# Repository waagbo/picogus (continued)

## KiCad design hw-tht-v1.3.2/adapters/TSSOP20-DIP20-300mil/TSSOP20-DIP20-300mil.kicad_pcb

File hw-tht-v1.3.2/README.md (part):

# PicoGUS THT (through-hole) v1.3.2 – based on PicoGUS v1.2

Board revision **v1.3.2**: the [v1.3.1 (rev B) THT board](../hw-tht-v1.3.1/README.md) on a 102 mm outline, with
the fine-pitch chips soldered straight to the card and a test pad on every one of their pins.

* **U3/U4** (SN74CB3T3257, TSSOP-16) and **U9** (PCM5100A, TSSOP-20) only exist as TSSOPs. They are soldered to
  the card on hand-solder footprints, and **every pin has its own 0.7 mm round test pad** in line with it, for a
  probe, a meter or a scope (see [U3/U4 and U9 with a test pad per pin](#u3u4-and-u9-with-a-test-pad-per-pin)).
  The TSSOP-to-DIP adapter boards of the earlier v1.3.2 layout are gone, and so are their sockets.
* **The GY-PCM5102 module option (J10) is gone.** The on-board DAC is always fitted.
* **New placement** of the DAC block, the mixer and the jacks (2026-10-31 / 2026-11-01): the DAC sits above U3/U4
  with its analog side facing east toward the output filter and the mixer above it, MIDI OUT at the top of the
  bracket end and LINE OUT below WT VOL (see [Placement](#placement)).
* **C36** (U9 charge-pump decoupling) is a through-hole 0.1 µF disc, and all eight DAC decoupling discs sit on the
  side of U9 where their pins are (see [DAC decoupling](#dac-decoupling)).
* **C8/C10** (U8 PSRAM decoupling) are the v1.3.1 through-hole discs, next to U8.
* **1.84 mm shorter**: 102.0 mm long over the outline (v1.3.1: 103.8 mm), trimmed at the bracket end. The bracket tab
  holes H1/H2 are 1.70 mm further from the bracket plate, so the card needs a bracket with longer tabs (see
  [Bracket](#bracket)).
* **No artwork on the back silkscreen**: the princess artwork is to be UV printed instead. The back texts stay.

The main board is through-hole apart from **U3, U4, U9** (TSSOP, 0.65 mm pitch), **U8** (APS6404L PSRAM, SOIC-8,
1.27 mm pitch) and the optional **U12** (USBLC6-2SC6, SOT-23-6), all on the front. The rest of the circuit is
v1.3.1's: USB-A host port, Waveblaster header, op-amp mixer.

> **Status: v1.3.2, ready to order (tag `hw-tht-v1.3.2`); not built or tested yet.** The placement of 2026-11-01 is
> routed on two layers (2026-11-01).
> The schematic's ERC is the same as v1.3.1's (280 warnings, 0 errors). DRC with schematic parity finds 0
> unconnected items and, as errors, only the 12 accepted courtyard overlaps in the logic column, so
> `hw-common/tools/jlcpcb.sh` exports with `FORCE=1`; `build/jlcpcb/` holds that export (not in git: the repository
> ignores `build/`). The first routed TSSOP layout (commit 298e993) was reviewed independently; this placement
> shortens the DAC outputs and the mixer's summing nodes that review pointed at, and its route applies the review's
> rules from the start. Compared with the routed DIP-adapter layout (commit d5c4a85) it is better on I2S, the
> DAC-to-mixer path and the vias at silkscreen text, and worse on the ISA data-bus length, which the test pads set:
> see [Layout status](#layout-status).

Files:

| File | What |
|---|---|
| `PicoGUS-THT.kicad_pro/.kicad_sch/.kicad_pcb` | KiCad **10** project (the root sheet is the v1.2 logic). The board is routed |
| `audio.kicad_sch` | PCM510x DAC sheet: U9 a TSSOP-20 with test pads, C36 a THT disc, no J10 |
| `wavetable.kicad_sch` | Waveblaster header, WT volume, op-amp mixer, line-out jack (as v1.3.1) |
| `usb.kicad_sch` | USB host port (J11 USB-A, F1, C34/C35, U12) (as v1.3.1) |
| `PicoGUS-THT-schematic.pdf` | Schematic PDF |
| `BOM-THT.csv` | BOM with DigiKey **and** LCSC part numbers and a digikey.no link per line (v1.3.0 lines checked 2026-09-28, rev B lines 2026-10-18, v1.3.2 lines 2026-10-23) |
| `BOM-THT-digikey-upload.csv` (+ `-optional`, `-10x`) | DigiKey cart/BOM upload with the reference designators as Customer Reference; optional: sockets, U12 |
| `BOM-THT-sockets.csv` (+ `-digikey-upload`, `-10x`) | Socket build: every DIP IC and the Pico socketed, with heights (see [Socket build](#socket-build)) |
| `docs/renders/` | 3D renders of the routed card from the front and the back, in red, purple, black and blue solder mask (ENIG, white silkscreen) |
| `docs/figures/` | Figures for the README's exceptions and design choices (e.g. the test pads, the placement options, the accepted courtyard overlaps), with the scripts that make them in `docs/figures/src/` |

The shared `PiGUS library` symbols and footprints are linked from `hw-common/`, like the other boards. **New in the
shared library for v1.3.2:** `TSSOP-16_4.4x5mm_P0.65mm_HandSolder_TestPads` (U3, U4),
`TSSOP-20_4.4x6.5mm_P0.65mm_HandSolder_TestPads` (U9) and `RPi_Pico_SMD_TH_USB_NoSWD` (U1, see
[102 mm board](#102-mm-board)), in `hw-common/PiGUS library.pretty`; DRC's library check finds the board's U1, U3,
U4 and U9 identical to them. The adapter footprints and adapter 3D models of the earlier v1.3.2 layout are removed;
the older `DIP-16_W7.62mm_TSSOP-16_Nested` stays unused.

Every part has a 3D model. The ones KiCad 10's library does not have are in `hw-common/parts`, reached through the
project folder's `parts` link: the CUI SJ1-3535NG jacks (J8 green; J5 a black copy of the same CUI model), the Alps
RK09712 pot (RV1) and a simple generated Bourns MF-R050 (F1). U3/U4/U9 use KiCad's TSSOP models, U1 KiCad's own
`RaspberryPi_Pico.step`, and J9's header model path is fixed. The library footprints carry the same models as the
board.

## What changed compared to v1.3.1

### U3/U4 and U9 with a test pad per pin

| | U3, U4 (SN74CB3T3257, TSSOP-16) | U9 (PCM5100A, TSSOP-20) |
|---|---|---|
| Footprint | `PiGUS library:TSSOP-16_4.4x5mm_P0.65mm_HandSolder_TestPads` | `PiGUS library:TSSOP-20_4.4x6.5mm_P0.65mm_HandSolder_TestPads` |
| Courtyard | 11.4 × 5.75 mm | 11.4 × 7.05 mm |
| Position (centre) | U3 (150.22, 110.10), U4 (161.44, 110.12), both 90° (pin 1 at the bottom left) | (156.10, 84.53), 180° (pin 1 at the bottom right) |

* **Land pattern**: the TSSOP hand-solder pads (1.775 × 0.40 mm at ±3.01 mm from the centre, toes out to ±3.9 mm),
  long enough to put an iron on each pin.
* **One test pad per pin**: a 0.7 mm round pad (bare copper, `testpoint` property) straight out from each pin,
  joined to it by a 0.2 mm track. The pads alternate between two columns, 4.45 and 5.10 mm from the centre, so each
  sits on its own pin's line and 1.3 mm from the next pad in its column; the track to an outer pad passes between two
  inner pads with 0.2 mm on each side, the board's normal clearance. The footprint has the pin numbers at the column
  ends in 0.8 mm silk. The pads make every pin reachable for a probe, a meter or a scope clip, and a solder bridge
  between two pins shows up as a short between their pads.
* **Routing**: an outer-column pin is routed from its test pad. An inner-column pin that is used gets a 0.2 mm
  escape stub straight on from its test pad, centred between the two outer pads, to 5.80 mm from the centre, and is
  routed from the stub end (26 stubs; the two left unused are removed after routing, see
  [Layout status](#layout-status)). The router cannot squeeze a track between two outer pads (0.6 mm
  gap) any other way, and the stubs keep the 0.2 mm clearance exactly as the pin-to-pad tracks do.
* **Pin numbers stay the schematic's**: U9 is 1 CPVDD, 2 CAPP, 3 CPGND, 4 CAPM, 5 VNEG, 6 OUTL, 7 OUTR, 8 AVDD,
  9 AGND, 10 DEMP, 11 FLT, 12 SCK, 13 BCK, 14 DIN, 15 LRCK, 16 FMT, 17 XSMT, 18 LDOO, 19 DGND, 20 DVDD.
* The symbols' `Adapter` fields and the adapter wording in the descriptions and sheet notes are gone; the root sheet
  says "SMD: U3/U4 TSSOP-16, U9 TSSOP-20 (with test pads), U8 SOIC-8, U12 opt.".

![Test pads on U9 (and U3/U4): the TSSOP-20 land pattern to scale with its 20 test pads in two staggered columns
(inner 4.45 mm, outer 5.10 mm from the centre, 1.3 mm between two pads of a column), the 0.2 mm track from each pin
to its pad passing between two pads with 0.2 mm clearance on each side, and the escape stubs that carry an
inner-column pin out between two outer pads to the routing](docs/figures/test-pads.png)

### No GY-PCM5102 module option

J10 (the GY-PCM5102 module, soldered on male pins over the DAC area as the alternative to the on-board DAC since
v1.3.0) is gone from the schematic and the board. Its dashed silkscreen outline and the "DAC -OR- GY-PCM5102"
heading went with it; the heading now just says "DAC". Its nets (BCK, DIN, LRCK, +5V, GND, AUDIO_L/R) stay,
because U9's circuit uses them. U9, C12–C20, C36, FB3, R7 and R8 are always fitted. The BOM's J10 line and its
"DAC AREA: leave out ..." notes are gone.

### DAC decoupling

C36 (U9 CPVDD decoupling) is the board's standard 0.1 µF 50 V X7R radial disc (Murata RDER71H104K0M1H03A, the 0.1 µF
line of the BOM) instead of v1.3.1's 0603. U9 stands at 180° with its analog pins 1–10 facing east, toward the output
filter and the mixer, and its digital pins 11–20 facing west. Each disc sits on the side of the pins it serves:

* **East, beside pins 1–10**, in rows 3.0 mm apart: C15 (AVDD, 10 µF) and C13 (AVDD) at the top, the output
  resistors R8/R7 level with pins 7/6, then C16 (CAPP/CAPM) and C17 (VNEG); the filter discs C20/C19 end the C13 and
  C16 rows on the east.
* **South, under pins 1–3**: C36 (CPVDD/CPGND), with C14 (+3V3) below it.
* **West, beside pins 11–20**: C18 (LDOO) level with pins 17–19 and C12 (DVDD) below pin 20. FB3 (the AVDD bead)
  runs along the top of the block from the +3V3 side in the west to its AVDD pad above C15.

Distances from the chip pin to the nearest pad of the part, straight line:

| Part | Pins | DIP-adapter layout (d5c4a85) | First routed TSSOP layout (298e993) | Now |
|---|---|---|---|---|
| C36 | CPVDD (1) / CPGND (3) | 2.7 / 9.2 mm | 9.7 / 5.6 mm | 3.6 / 5.4 mm |
| C16 | CAPP (2) / CAPM (4) | 3.2 / 3.2 mm | 9.5 / 4.6 mm | 9.7 / 5.5 mm |
| C17 | VNEG (5) | 6.6 mm | 9.6 mm | 8.1 mm |
| C13 | AVDD (8) / AGND (9) | 4.7 / 6.7 mm | 5.1 / 9.6 mm | 5.6 / 9.9 mm |
| C15 | AVDD (8) | 7.3 mm | 12.4 mm | 7.8 mm |
| C18 | LDOO (18) / DGND (19) | 3.5 / 9.1 mm | 4.5 / 9.5 mm | 4.0 / 9.0 mm |
| C12 | DVDD (20) / DGND (19) | 4.5 / 8.4 mm | 2.6 / 6.4 mm | 5.4 / 3.8 mm |
| R7 / R8 | OUTL (6) / OUTR (7) | 3.0 / 2.8 mm | 6.8 / 8.2 mm | 4.7 / 4.6 mm |
| FB3 | AVDD (8) | 2.8 mm | 14.1 mm | 6.3 mm |

* **C36 is the nearest disc to its pin** (3.6 mm from CPVDD), as the PCM510x datasheet asks for the charge-pump
  supply. C16 (the flying capacitor between CAPP and CAPM) stays 9.7 mm from CAPP: it shares the east column with
  the output resistors, which sit level with their pins.
* C16 and C17 were 0.02 mm off the 3.0 mm row grid in the uploaded placement (y 88.60 / 91.60), so C16's courtyard
  touched R7's by 0.015 mm; they are now at y 88.62 / 91.62, in line with C19.
### C8/C10: through-hole discs next to U8

| Ref | Part | DigiKey | LCSC |
|---|---|---|---|
| C8 | 0.1 µF 50 V X7R radial disc, 5.0 mm pitch, Murata RDER71H104K0M1H03A (the BOM's 0.1 µF line) | 490-9144-1-ND | C527620 |
| C10 | 1 µF 50 V X7R radial disc, 5.0 mm pitch, Murata RDER71H105K2M1H03A | 490-9146-1-ND | C1620132 |

These are the v1.3.1 parts again (the routed layout of commit 8dbb6c6 had 0805s on the back under U8). U8 (SOIC-8,
front) stands at 90° at (190.00, 92.47): pins 1–4 along the bottom (y 94.95, pin 1 at the left), pins 5–8 along the
top (y 90.00), pin 8 (+3V3) at (188.09, 90.00), pins 3/4/7 GND. C8 (0.1 µF) stands vertically left of U8, its +3V3
pad 2.50 mm straight left of pin 8 at (185.59, 90.00) and its GND pad at (185.59, 95.00); C10 (1 µF) lies above U8,
+3V3 pad at (187.09, 87.00), GND pad at (192.09, 87.00). With them, every SMD part (U3, U4, U8, U9, U12) is on the
front.

### 102 mm board

The bracket end of the outline is trimmed 1.84 mm (x 220.13 → 218.29). The board is 101.90 × 99.85 mm at the
outline's line centres, 102.00 × 99.95 mm over its 0.1 mm lines (v1.3.1 and the routed v1.3.2 layout: 103.74 ×
99.85 / 103.84 × 99.95 mm). JLCPCB quoted USD 24.50 for 10 black ENIG 2-layer boards at 102.0 mm (and 101.9 mm), USD 33 at
102.7 mm and 33.53 at 103.74 mm (2026-10-28). The ISA fingers, the other three edges and the bracket plate's place in the case do not change.
To keep copper at least 0.35 mm from the new edge, these parts moved left, away from the bracket:

| Part | Moved | Now | Nearest copper to the new edge |
|---|---|---|---|
| H1 / H2 (bracket tab holes) | 1.70 mm | x 214.70 | 0.39 mm (their 6.4 mm pads) |
| J5 (MIDI out) | 1.10 mm | x 217.00 | 0.39 mm (sleeve pad) |
| J8 (line out) | 0.90 mm | x 217.00 | 0.39 mm (sleeve pad) |
| U1 (Pico), with its five test-pad rule areas and its two micro-USB relief slots | 1.35 mm | centre x 192.88, pin 1 (217.01, 100.00) | 0.36 mm (TP2/TP3); the slots (centre x 216.88) end 0.41 mm from the edge |
| U4 / U3 | – | TSSOP centres x 161.44 / 150.22 (re-placed for the soldered TSSOPs, see [Placement](#placement)) | – |

J11 and RV1 stay where they were. The distances are to the outline's line centre. Between these parts and the edge
there is no room for a track or a via: 0.3 mm copper-to-edge, a 0.2 mm track and 0.2 mm clearance need 0.7 mm. What
the trim means for the bracket is under [Bracket](#bracket): the tab holes need a bracket with 1.70 mm longer tabs.

![The bracket end trimmed from 103.74 to 101.90 mm: old (dashed) and new outline with the trimmed 1.84 mm strip, the
bracket plate and tabs from User.Drawings, the tab holes H1/H2 1.70 mm further in (7.03 mm from the plate instead of
5.33), J5, RV1, J8, J11 and the Pico's USB end with their moves and nearest copper to the new edge, and a table of the
x positions](docs/figures/bracket-trim.png)

* **U1 uses the new footprint `PiGUS library:RPi_Pico_SMD_TH_USB_NoSWD`**: `RPi_Pico_SMD_TH_USB` without the
  three SMD castellation pads at the SWD end (pads 41–43: SWCLK and SWDIO, both not connected, and GND; their
  through-holes stay) and with the courtyard 0.2 mm past the module there instead of 0.5 mm. With the old
  courtyard, U4's would overlap the Pico's by 0.25 mm.
* The Pico's USB end (x 218.38) is now flush with the edge: 0.09 mm past the outline's line centre (0.40 mm inside
  it before).
* The Pico's far end is at x 167.38, 2.9 mm under a full-size Waveblaster daughterboard's outline (x 170.32; routed
  v1.3.2 layout 1.6 mm, v1.3.1 1.3 mm). That matters for a socketed Pico (see [Socket build](#socket-build)).

### Placement

The board holds a hand arrangement on the 102 mm outline: the logic column and the Pico from 2026-10-28, the jack
arrangement for the soldered TSSOPs from 2026-10-31, and the DAC block and mixer as rearranged on 2026-11-01 after a
first route, routed afterwards (see [Layout status](#layout-status)).

* **Logic column at the left edge** (as on the earlier v1.3.2 layout). U10, U7, U6 and U5 (DIP-14, 90°, pin 1 at the
  left as on v1.3.1) are stacked in line with U2 at x 120.07, 12.05 mm apart (pin 1 at y 65.62 / 77.67 / 89.71 /
  101.76; U2: 113.81). Each chip's decoupling cap lies horizontally (0°) in the gap above it, pad 1 2.21 mm straight
  above the supply pin (pin 14; U2: pin 20): C21 (U10, +5V), C6 (U7), C9 (U6), C7 (U5) and C4 (U2), pads at x
  120.07 / 125.07, y 55.79 / 67.83 / 79.88 / 91.93 / 103.97. R18, R5, R6 and R17 stand vertically (−90°) in one
  column at x 138.60, at the chips' right-hand ends (pad 1 at y 56.73 / 68.78 / 80.82 / 92.87). The column is
  packed tighter than the courtyards allow: 12 overlaps, accepted (see [Layout status](#layout-status)). The five
  references stand vertically at the board edge (x 117.50), centred on each chip.
* **U2** (DIP-20, 90°) at the lower left, pin 1 (120.07, 113.81). **J1** (the IRQ/DMA jumper block) at pin 1
  (136.03, 124.91), 90°, with its `IRQ`/`DMA` labels and numbers above it.
* **U3/U4** (TSSOP-16 with test pads, 90°): U3 (D0–D3, A0–A3) at (150.22, 110.10) and U4 (D4–D7, A4–A7) at
  (161.44, 110.12), pin 1 at the bottom left. Their decoupling discs C3/C5 lie above them at y 102.29 (C3's +3V3 pad
  at x 147.88, 4.8 mm from U3's pin 16), R2 at (160.97, 99.01).
* **DAC block, above U3/U4 and the Pico's far end**: U9 (TSSOP-20 with test pads) at (156.10, 84.53), 180°: pins
  11–20 (I2S, LDOO, DGND, DVDD) on its west side, pins 1–10 (charge pump, VNEG, outputs, AVDD, AGND) on its east side,
  facing the output filter and the mixer. East of it, in rows 3.0 mm apart (see [DAC decoupling](#dac-decoupling)):
  C15 (163.60, 76.53), C13 (168.60, 79.53), R8 (163.60, 82.60), R7 (163.62, 85.62), C16 (168.60, 88.62) and C17
  (163.60, 91.62), with the filter discs C20 (170.70, 79.53) and C19 (170.70, 88.62) at the east end. C36 (161.00,
  90.50) and C14 (156.00, 93.50) lie under U9's pins 1–3, C18 (149.10, 86.03) and C12 (153.60, 90.53) on its west
  side, and FB3 (the AVDD bead) along the top at (148.60, 77.03). `DAC` stands at (146.11, 92.10).
* **Mixer, above the DAC block**: U11 (DIP-8, 0°) at (173.00, 61.00), its feedback discs C30/C31 standing (90°) at
  its two ends, (170.12, 65.08) and (183.50, 67.00); C28 (+12VA) above it at (180.62, 54.08) and C29 (−12VA) below at
  (175.62, 75.08); R23/R24 (±12V 10 Ω) at (170.42, 57.50) / (170.42, 72.00); C32/C33 (47 µF) standing at x 184.62
  (y 57.12 / 70.08). The mixer resistors stay in two columns: R13, R11, R22, R10, R21 at x 189.43 (y 54.50 / 58.00 /
  65.00 / 72.50 / 79.50) and R20, R12, R19 at x 199.58 (y 61.50 / 69.00 / 76.00). `MIXER` at (171.12, 55.04).
* **C22/C23** (the 10 µF bipolar Waveblaster coupling caps) stand at the top next to J9, (174.00, 40.00) and
  (181.50, 40.00), −90°, with their references above them at y 38.00. C22's can is 0.48 mm outside a full-size
  daughterboard's outline (x 170.32) at nominal size.
* **Bracket end, top to bottom: MIDI OUT, WT VOL, LINE OUT.** J5 (MIDI out) at (217.00, 49.00) with its parts
  R3 (176.64, 46.50), R4 (186.80, 50.50), FB1 (189.50, 46.50) and FB2 (189.50, 50.50) along the top; RV1 (WT VOL)
  at (214.00, 61.40); J8 (line out) at (217.00, 75.50). The labels
  `MIDI OUT`, `WT VOL` and `LINE OUT` are left-aligned at x 204.0 (y 43.5 / 65.0 / 70.0).
* **USB host corner**: U8 (SOIC-8) at (190.00, 92.47), 90°, with C8/C10 next to it (see
  [C8/C10](#c8c10-through-hole-discs-next-to-u8)); U12 at (197.14, 91.45), F1 vertical at (204.00, 90.00), C35 at
  (200.00, 95.00), C34 at (202.30, 83.50).
* **Waveblaster side**: R16 at (150.00, 46.00), 0°; C24, C25 and C26 in a row at y 45.50 (x 146.90 / 143.00 /
  139.00).
* **Pico (U1)** at (192.88, 108.89), pin 1 (217.01, 100.00), and the bracket end (H1/H2, J11) as on the earlier
  v1.3.2 layout (see [102 mm board](#102-mm-board)).

**Why this arrangement.** Four placements of the DAC, mixer and jacks were compared before the first route, each
with the DAC discs on their pins and the logic-column labels as above: A (the first hand placement, DAC block high in
the middle), A2 (A with a DAC block turned 90°), C (that block in the middle with the mixer beside it) and D. In A2
and C, U9's I2S pins face away from the Pico, and a trial route of the three I2S nets alone (with the DAC outputs kept
clear) needed 232 and 238 mm; in A 171 mm; in D 122 mm. D had the shortest DAC-to-mixer path and the shortest
ratsnest overall and was routed first (commit 298e993). That route left the mixer's summing nodes 51 / 53 mm long
and the DAC outputs 19 / 20 mm, because the output filter sat above U9 and the mixer inputs far from U11. The
present arrangement keeps D's jacks and moves the DAC block 12.9 mm west with the output filter east of U9, between
it and the mixer, and turns U11 so that its feedback discs sit on its pins. Against D, in ratsnest length: summing
nodes 95.7 → 61.9 mm, DAC outputs 18.5 → 9.5 mm, mixer outputs 64.3 → 41.5 mm, AVDD and LDOO 26.5 → 15.6 mm; I2S
113.6 → 123.5 mm and the Waveblaster path behind C22/C23 56.0 → 75.4 mm are longer; all nets but GND 4229 → 4169 mm.

![The comparison before the first route (D became commit 298e993; the present arrangement grew out of it). Placements A, A2, C and D side by side: board outlines with the DAC area and the mixer area shaded, the I2S
ratsnest, the audio-path ratsnest and the digital ratsnest that crosses the DAC area, and a table of the trial I2S
route, I2S ratsnest, distances from the DAC area to the Pico and U8, digital ratsnest through the DAC and mixer areas,
DAC-to-mixer and Waveblaster paths, mixer summing nodes, line out, ±12V, SPI and total ratsnest](docs/figures/placement-options.png)

| Part | Routed DIP-adapter layout (d5c4a85) | Now |
|---|---|---|
| U3 / U4 | DIP-16 adapter pin 1 (146.53, 106.42) / (157.74, 106.44), 0° | TSSOP-16 centre (150.22, 110.10) / (161.44, 110.12), 90° |
| U9 | DIP-20 adapter pin 1 (146.00, 78.30), 90° | TSSOP-20 centre (156.10, 84.53), 180° |
| U11 | (173.02, 51.10), 90° | (173.00, 61.00), 0° |
| J5 (MIDI) / J8 (line out) | (217.00, 75.50) / (217.00, 49.10) | (217.00, 49.00) / (217.00, 75.50) |
| U8 | (189.00, 93.90), 0° | (190.00, 92.47), 90° |
| C8 / C10 | (191.50, 88.40) / (184.00, 88.40), 180° | (185.59, 90.00), −90° / (187.09, 87.00), 0° |
| J1 | (120.00, 123.70) | (136.03, 124.91) |
| FB3 | (164.10, 93.73), 90° | (148.60, 77.03), 0° |
| C3 / C5 | (153.50, 103.28) / (164.69, 103.34), 180° | (147.88, 102.29) / (158.88, 102.29), 0° |

Positions are footprint origins (pin 1 for the DIPs, the centre for the TSSOPs), in mm. 51 of the 88 footprints moved
against the DIP-adapter layout (29 against the first routed TSSOP layout, 298e993); the logic column, U1, U2, the Waveblaster header and the bracket-end parts other
than J5/J8 did not.

### Silkscreen and back artwork

* Front `v1.3.2`, back `PicoGUS v1.3.2`.
* **Label font: Jost, embedded in the board file.** The 21 board labels (`WAVEBLASTER`, `MIXER`, `DAC`, `v1.3.2`,
  `LINE OUT`, `WT VOL`, `MIDI OUT`, `UART`, `USB PWR`, `IRQ`/`DMA` and their numbers, `< REAR`) use Jost Medium and
  Bold ([indestructible-type/Jost](https://github.com/indestructible-type/Jost), SIL Open Font License 1.1; the
  copyright and licence are in the font files' metadata), embedded with the board's embedded-fonts option. KiCad
  therefore shows and plots them the same on every machine, with or without the font installed. They were in
  Futura, inherited from v1.2, which was not embedded: each machine plotted its own substitute (DejaVu Sans or Inter
  in the cloud sessions that made the earlier gerbers). Futura cannot be embedded: Futura PT is marked
  "Preview & Print" only, so KiCad refuses it, and its licence forbids sharing the files. Jost is a free
  Futura-style face and looks almost the same at this size. Embedding adds about 120 KB to the board file. The
  v1.3.1 and v1.3.0 boards still use un-embedded Futura.
* **No princess artwork on the board.** It is removed from the back silkscreen and is to be UV printed on the back
  instead (source: `hw-common/art/princess.svg`; the routed v1.3.2 layout had it at 52.8 × 27.0 mm, v1.3.1 at
  71.6 × 37.0 mm). The back text block (version, copyright, licence, URL, thanks, dedication) and `< REAR` stay.
* **Front copper logo moved.** The exposed-copper PicoGUS logo (F.Mask openings over the front GND pour, with a rule
  area that keeps tracks and vias out) is turned horizontal and sits along the top edge above `LINE OUT`, x
  185.9–211.6, y 37.8–40.6, with `v1.3.2` right of it at (214.1, 40.0). Before, the logo stood vertically at the left
  edge (x 118.3–121.1, y 43.5–69.3) and `v1.3.2` at (120.5, 40.5). The pour under it is filled, so the logo shows
  copper.
* Labels placed by hand (2026-10-31; `MIXER`, `DAC` and C22/C23 on 2026-11-01). `MIXER` (171.12, 55.04) and `DAC`
  (146.11, 92.10) are centred, 1.2 mm high
  like the bracket-side labels (`DAC` was vertical at (186.3, 74.5) on v1.3.1). `WAVEBLASTER` is 1.2 mm (was 0.8),
  centred at (143.65, 37.5). `MIDI OUT`, `WT VOL` and `LINE OUT` are left-aligned at x 204.0 (y 43.5 / 65.0 / 70.0),
  `UART` and `USB PWR` at x 208.2 (y 121.5 / 126.0), so `UART` no longer touches J6's outline. The references of the
  logic column (U10, U7, U6, U5, U2) stand vertically at the board edge (x 117.50), centred on each chip; the
  references of the discs sit in the middle of each disc. The references of C22, C23, C32, C33, C34, U8, U12 and J11
  were placed by hand (C22's and C23's above their cans at y 38.00); U8's stands at (185.00, 88.00), nearer C10 than U8, and U12's is 0.08 mm from neighbouring silk.
  `< REAR` moved 1.70 mm left with H1/H2, its arrow tip still in line with them.
* **No via hole in any label**: the router counted every front and back silk text as a no-via area, so no via hole
  is within 0.10 mm of any text (the earlier routed layout had 13).
* v1.3.1's U12 pin-1 dot, left behind at (201.5, 89.7) next to F1 when U12 moved, is removed.
* Silkscreen DRC (with silk_over_copper/silk_overlap enabled): 45 silk_over_copper, all from the outlines of the
  decoupling discs in the logic column crossing the neighbouring DIP pads (`jlcpcb.sh` plots the silkscreen with the
  mask openings subtracted, so none of it prints on a pad); 2 silk_overlap (the IRQ/DMA divider line over J1 twice,
  as on v1.3.1); 19 silk_edge_clearance (J8, J5, RV1, J11 and the Pico's outline at
  the bracket end).

### Other

* Title blocks say v1.3.2 (root sheet and board 2026-10-28, the other sheets 2026-10-23). The schematic notes about
  the GY module and the SMD parts are updated, and `PicoGUS-THT-schematic.pdf` is plotted from the current schematic.
* No reference designator changed and none is new; J10 is the only one removed. The design rules and net classes
  are v1.3.1's (the `.kicad_pro` is unchanged).
* The schematic fields of C8/C10 name the Murata discs again (as on v1.3.1), and U1's footprint field is
  `PiGUS library:RPi_Pico_SMD_TH_USB_NoSWD`.
* 32 footprints (the wavetable sheet set, FB3, RV1, U11) still carried symbol links (KIID paths) from before the
  v1.3.0 schematic rebuild; DRC parity had only matched them by reference. They are re-linked to their symbols, so
  "Update PCB from schematic" keeps them.
* The U3/U4/U9 symbols point at the new TSSOP footprints with test pads; their `Adapter` fields are removed, and the
  sheet notes say "soldered to the card" (C36's note: "close to U9 pins 1 (CPVDD) and 3 (CPGND)").

## Layout status

The placement of 2026-11-01 is routed on two layers (2026-11-01). It replaces a first routed TSSOP layout (commit
298e993) whose route was reviewed independently from the analog/power and the digital/manufacturing side; the rules
that review led to are applied to this route from the start (see [Review](#review)). The comparison is with that
layout and with the routed DIP-adapter layout of commit d5c4a85 (same netlist apart from the U3/U4/U9 footprints),
measured with the same scripts; d5c4a85's README (`git show d5c4a85:hw-tht-v1.3.2/README.md`) compares it with
8dbb6c6 and v1.3.1.

### Routing

* **Test-pad fan-out first**: the 52 pin-to-test-pad tracks and 26 escape stubs (see
  [U3/U4 and U9 with a test pad per pin](#u3u4-and-u9-with-a-test-pad-per-pin)) are fixed copper; the router lands
  on the outer test pads and the stub ends. The stubs of U9's CPGND (3) and AGND (9) ended up unused and were
  removed (24 remain); both pins reach ground through the front pour around U9.
* **U9's east side by hand.** On U9's analog side the pins come out OUTR, OUTL, VNEG, CAPM, CPGND, CAPP from the
  top, while their parts stand in a column 2.4 mm east of the test pads (R8, R7, C16, C17) with room for one track
  between the two. On one layer DAC_OUTL, VNEG, CAPM and CAPP have to cross, and the grid router could not place a
  via that close to the test pads. These four nets are routed by hand: DAC_OUTL on the front to R7; VNEG through a
  via just past its stub and on the back under the test pads to C17; CAPM on the front between R7 and a CAPP via to
  C16; CAPP through that via and on the back to C16's far pad. All at least 0.207 mm from other copper.
* **Grid router** (negotiated-congestion rip-up and re-route, as for the earlier layouts) for everything else, then
  polished, a GND pass (pours on both layers, stitching vias) and clean-up steps, each kept only if DRC stayed clean:
  redundant vias, GND finger tracks, stitching along the copper logo, thermal stubs, power widened up to 0.8 mm where
  it fits, vias moved off other-net pads, acute pad entries squared, power entries necked beside the gold fingers.
* **DAC block kept clear.** Digital, I2S and USB nets pay a cost within 1 mm of the audio copper, the DAC outputs and
  the DAC's analog nets (AVDD, VNEG, CAPP/CAPM, LDOO), and may not enter the block's analog half (east of U9, up to
  the output-filter discs) or the area under U9. −12V, +12V, ~RI/OCHRDY and +5V may not enter the DAC block at all,
  +5V also not the mixer. No track but GND runs on the front under U9, so the front pour under the chip is one piece;
  4 GND vias (3 under the body) tie it to the back pour.
* **I2S may change layers** (via cost lowered): DIN and BCK leave U9 in the opposite order to the Pico's pins, so one
  of them has to cross the other.
* **Labels are no-via areas**: no via hole is within 0.10 mm of any silk text, front or back.
* Design rules unchanged (the `.kicad_pro` is v1.3.1's): 0.2 mm clearance, 0.3 mm copper to edge, 0.25 mm default
  track and 0.7/0.35 mm vias, `pwr` 0.4 mm and `GND` 0.5 mm with 0.8/0.4 mm vias, `audio` with 0.6 mm clearance.
  The 0.2 mm test-pad tracks and stubs, the centred 0.2 mm necks of +5V, +3V3 and ±12V between Pico and U2 pins and
  short jogs at pads are narrower than their class.
* 5494 mm of track and 422 vias: 205 GND, 26 power, 191 signal (756 plated holes with the THT pads).
* DRC with schematic parity: 0 unconnected items, and as errors only the 12 accepted courtyard overlaps below, so
  `jlcpcb.sh` needs `FORCE=1`. Warnings: 3 `lib_footprint_mismatch` (J3, J11, RV1; expected, see
  [Kept from v1.3.1](#kept-from-v131)), 19 `silk_edge_clearance`, 8 `starved_thermal` and 83 schematic-parity field
  warnings (footprints without the symbols' Manufacturer/MPN fields, J3's BOM flag). The starved thermals are J9's
  GND pins 7, 11, 15 and 25, U7 pin 10 and U2 pin 10 (GND) and the Pico's GND pin 33 on both its pads: each has one
  spoke on the side where signal tracks pass close, and joins the pours with two or three spokes on the other side or
  through 0.5 mm GND tracks.

  ![The 8 starved thermal reliefs: J9 pins 7, 11, 15 and 25, U7 pin 10, U2 pin 10 and Pico pin 33
  (also on its castellation pad), each with one spoke where signal tracks pass close, and how each joins the GND
  pours on the other side](docs/figures/starved-thermals.png)

* **Courtyard overlaps (accepted), all in the logic column**: each decoupling disc's courtyard overlaps those of the
  DIPs above and below it by 0.33–0.34 mm (C21/U10, C6/U10, C6/U7, C9/U7, C9/U6, C7/U6, C7/U5, C4/U5, C4/U2), and
  the vertical resistors' overlap end to end by 0.20 mm (R18/R5, R5/R6, R6/R17). The disc bodies (F.Fab) stay about
  1.6 mm from the DIP bodies and 0.16 mm (seen from above) from the DIP pads; the discs' pads are 0.61 mm from the
  DIP pads. The resistors' pads are 0.29 mm apart end to end (GND/RESET, GND/+5V, DACK/+3V3): solder those with
  care.

  ![The 12 courtyard overlaps: 3D render, courtyard map with each overlap's depth, and close-ups of a disc between two
  DIPs and of two resistors end to end](docs/figures/courtyard-overlaps.png)

### Review

The first routed TSSOP layout (298e993) was reviewed independently; its findings shaped this route's rules:

* **U9's front ground**: AVDD, I2S, DAC_OUTL and ~RDACK ran under the chip there. Here nothing but GND runs on the
  front under U9, and 4 GND vias (3 under the body) tie that pour to the back. A 0.8 mm +3V3 track (DVDD pin 20 to
  CPVDD pin 1 and C36) runs along the chip's south edge, 0.12 mm outside its body.
* **Supplies through the analog area**: +5V is kept out of the DAC block and the mixer, −12V and +12V out of the DAC
  block (0 mm² of +5V and +12V there; −12V touches the block's edge with 0.017 mm²).
* **Digital next to the DAC's analog nets**: none within 1 mm of AVDD, VNEG, CAPP/CAPM or LDOO; the nearest is LRCK
  1.33 mm from LDOO on its way to U9's west pins. The nearest digital copper to U9's pins 1–10 is an RA9 via 3.6 mm
  away. No digital track or via is within 1 mm of any audio net.
* **Gold fingers**: no power copper within 0.30 mm of an other-net finger (the nearest power entries are 0.40 mm or
  more away), and no copper sticks out of a finger into the opening between the fingers.

  ![Solder side above J3's B-row fingers on 8dbb6c6 and on v1.3.2: an overview of B1-B31 and the no-fill strip,
  then close-ups of B5-B11 (±12V) and B28-B31 (+5V). Each finger is its own mask opening and only mask lies between
  a finger top (y 128.97) and the opening between the fingers (y 129.60)](docs/figures/gold-fingers.png)

  ![The GND tracks from the ground fingers B1, B10 and B31 on v1.3.2: B10's track 1.0 mm, then 0.5 mm
  for 2.6 mm past C1's +3V3 pad (0.22 mm) to the back pour, 6.6 mm in all; B1 and B31 1.0 mm straight into the pour;
  B10 on 8dbb6c6 for comparison](docs/figures/b10-ground-finger.png)

* **Mixer summing nodes and DAC outputs**: long on 298e993 (51 / 53 mm and 19 / 20 mm), set by that placement. The
  present placement shortens them (see [Placement](#placement)); routed they are 44.4 / 28.6 mm and 5.8 / 4.9 mm.

### Compared with the earlier routed layouts

| | DIP adapters (d5c4a85) | first TSSOP layout (298e993) | v1.3.2 now |
|---|---|---|---|
| DRC errors / unconnected (schematic parity) | 12 / 0 | 12 / 0 | 12 / 0 (the accepted courtyard overlaps) |
| starved_thermal warnings | 6 | 7 | 8 |
| Track / vias (GND / power / signal) | 5504 mm / 445 (194 / 32 / 219) | 5587 mm / 450 (214 / 29 / 207) | 5494 mm / 422 (205 / 26 / 191) |
| ISA D0–D7 length / vias | 283 mm / 21 | 407 mm / 26 | 350 mm / 18 |
| I2S length / vias | 261 mm / 6 | 187 mm / 16 | 186 mm / 5 |
| USB D+ / D− length | 51.3 / 43.8 mm | 48.1 / 45.6 mm | 46.3 / 46.2 mm |
| +12V / −12V length (vias) | 125 (0) / 159 (5) mm | 146 (6) / 139 (4) mm | 153 (5) / 142 (4) mm |
| DAC_OUTL / DAC_OUTR (U9 to R7/R8) | 3.3 / 3.0 mm | 18.9 / 19.9 mm | 5.8 / 4.9 mm |
| AUDIO_L / AUDIO_R (filter to mixer) | 44.0 / 59.2 mm | 11.4 / 43.7 mm | 24.8 / 34.2 mm |
| Mixer summing nodes U11.2 / U11.6 | 14.6 / 36.1 mm | 51.3 / 52.5 mm | 44.4 / 28.6 mm |
| Digital tracks and vias within 1 mm of audio copper | none | none | none |
| Other-net track within 1 mm of audio copper, same layer | 11.4 mm | 21.5 mm | 22.3 mm (17 mm of it U9's own nets at its pins) |
| Supply copper in the DAC block: +5V / −12V / +12V | – | 0 / 0 / 2.9 mm² | 0 / 0.02 / 0 mm² |
| Line-out ground error per ampere of loop current from J8's sleeve to the fingers, worst channel: no Waveblaster / Waveblaster at full volume | 285 / 466 µV/A | 1019 / 292 µV/A | 868 / 334 µV/A |
| same, loop current to the bracket (H1/H2) | 313 / 223 µV/A | 466 / 253 µV/A | 437 / 280 µV/A |
| Line-out ground error at 500 mA of USB-host load, worst channel: no Waveblaster / at full volume | 128 / 133 µV | 269 / 258 µV | 211 / 26 µV |
| Power copper within 0.30 mm of an other-net gold finger | none | none | none |
| Vias < 0.5 / < 1.0 mm from a gold finger | 0 / 0 | 0 / 1 | 0 / 1 |
| Vias < 0.30 / < 0.25 mm from an other-net pad | 0 / 0 | 3 / 1 | 2 / 1 |
| Via holes < 0.10 mm from silk text (inside the ink) | 7 (4) | 0 (0) | 0 (0) |

All columns come from the same scripts. The line-out rows come from the DC copper model described in d5c4a85's README
(refilled pours, 0.1 mm grid, the Pico's GND pins tied; `e = (Vref − Vsleeve) + 0.977·(Vref − V(U9.9)) + 2·(Vref − Vwt)`).
The figures compare v1.3.2 with 8dbb6c6, the 103.7 mm layout that README compared against.

**Better** than 298e993: the DAC outputs, the summing nodes and AUDIO_R, I2S vias, the ISA data bus, fewer vias
overall, +12V kept out of the DAC block, the line-out ground error without a Waveblaster (868 against 1019 µV/A for a loop to the
fingers) and from USB load (211 against 269 µV). **Worse**: AUDIO_L (the filter sits east of U9, the mixer input to
the north-east), +12V length, the line-out ground error with a Waveblaster at full volume (334 against 292 µV/A to the
fingers, 280 against 253 to the bracket). Against d5c4a85 the ISA data bus is still longer, the DAC outputs and summing
nodes slightly longer, as the placement sets them, and so is the line-out ground error from a loop through the
line-out cable (868 against 285 µV/A without a Waveblaster).

### Known weaker points (accepted)

* **Hand-routed corner east of U9**: the VNEG via is 0.216 mm from R7's DAC_OUTL pad (DRC minimum 0.20 mm), and
  CAPM passes R7's pad at 0.207 mm. Inspect that corner after soldering R7.
* **Audio beside other copper** (22.3 mm within 1 mm, same layer): U9's own AVDD, CAPM, VNEG and CAPP beside
  DAC_OUTL/R where they leave the neighbouring pins (17 mm, from 0.10 mm at the test pads), −12V along R24 (its own
  feed resistor into the mixer; 2.7 mm at 0.68 mm) and at the top left (2.3 mm, 0.62 mm, as on d5c4a85).
* **ISA data bus**: D0–D7 are 350 mm with 18 vias (d5c4a85 283 mm / 21; D2 69 mm with 6 vias), as U3/U4 moved to
  make room for their test pads. Irrelevant at ISA speed.
* **Digital in the DAC block's digital half**: besides I2S, ~RIOW, ~RIOR, I/OCHRDY and RA9 cross the block west and
  south of U9 (the side of its digital pins and of C12/C14/C18), at least 3.6 mm from pins 1–10.
* **Vias near other-net pads**: besides the VNEG via above, an RA9 via is 0.266 mm from the Pico's pin 18 (GND).
* **U9's ground pins** (CPGND, AGND, DEMP, FLT, SCK, FMT, DGND) reach a GND via 0.8–4.5 mm away (CPGND the farthest),
  through the front pour that surrounds the chip.
* **Line-out ground loop**: per ampere of loop current from J8's sleeve to the fingers, the ground error at the
  jack is 868 µV (left channel, no Waveblaster, RV1 turned down; d5c4a85 285 µV, 298e993 1019 µV), and 437 µV to
  the bracket. With 10 mA of loop current that is 8.7 µV through the fingers and 4.4 µV through the bracket: below
  −100 dBV, under the DAC's noise floor (about 21 µV) and 100–300× less than the drop along the cable shield itself.
  The bracket path only exists with a metal bracket screwed to the chassis; a 3D-printed bracket carries no loop
  current. 500 mA of USB-host load adds 211 µV at the worst channel (d5c4a85 128 µV).

  ![Line-out ground loop: ground-potential maps of the board for 1 A from J8's sleeve to the bracket tab holes H1/H2
  and to the ISA GND fingers, with U11.3/U11.5 and U9.9 marked; the worst-channel line-out ground error against
  8dbb6c6 (fingers 868 / 334 against 410 / 715 µV/A, bracket 437 / 280 against 185 / 166 µV/A, 500 mA USB load
  211 / 26 against 226 / 314 µV); and at 10 mA of loop current, 4.4-8.7 µV next to the DAC's 21 µV noise floor and
  1-3 mV across a cable shield](docs/figures/groundloop.png)

* **B10's GND track**: 1.0 mm for 4.0 mm, then 0.5 mm for 2.6 mm (past C1's +3V3 pad at 0.22 mm) before it reaches
  the back pour, 6.6 mm in all; B1 and B31, the other two ground fingers, run 1.0 mm straight into the pour.
* **Silk**: no via hole touches any text. U8's reference stands nearer C10 than U8 and U12's is 0.08 mm from
  neighbouring silk (both placed by hand, left as placed).

  ![Via holes near silkscreen text: none is within 0.10 mm of any text on either side; the six nearest
  are 0.15 to 0.17 mm away (U10, `< REAR`, U11, U9's pin-number text, `DMA`, F1)](docs/figures/silk-vias.png)

* **I2S around the DAC**, for reference:

  ![BCK, DIN and LRCK from the Pico to the DAC U9 on v1.3.2 and on 8dbb6c6, both copper layers, with
  U9's analog pins 1-10, the CAPP/CAPM/VNEG/AVDD copper and the audio-class copper inside a 1 mm keep-away. v1.3.2:
  185.7 mm and 5 vias to U9's west pins, 5.04 mm from pins 1-10, no digital copper inside the keep-away; close-ups
  of U9 and of the hand-routed corner east of it. 8dbb6c6: 235.5 mm and 1 via; LRCK passes U9 pin 1 at 0.33 mm](docs/figures/i2s-around-dac.png)

### Before ordering and building

* **Bracket**: get or print a bracket whose tabs are 1.70 mm longer than a Keystone 9202's (see [Bracket](#bracket)).
* In JLCPCB's placement preview, check pin 1 of U3, U4, U8, U9 and U12.
* **Solder the TSSOPs first** and check them on their test pads (see [Ordering](#ordering)).
* **Solder J11 before the Pico** and check the gap between its shield pad and Pico pin 4 (SPI_SCK, 0.80 mm) for a
  bridge (see [Kept from v1.3.1](#kept-from-v131)).

## Socket build

`BOM-THT-sockets.csv` (with `BOM-THT-sockets-digikey-upload.csv` and `-10x`) lists everything needed to build the
card with every DIP IC and the Pico socketed. The same parts are the optional socket lines of `BOM-THT.csv`. U3, U4
and U9 are soldered TSSOPs and U8/U12 SMD parts: they are never socketed.

| Socket for | Part (DigiKey) | Height above the board | Top of the part |
|---|---|---|---|
| U2 (DIP-20) | On Shore SA203000 (ED3020-ND) | 4.6 mm | ≤ 9.8 mm, **under the daughterboard** |
| U5, U6, U7, U10 (DIP-14 ×4) | Adam Tech ICM-314-1-GT-HT (2057-ICM-314-1-GT-HT-ND) | 4.6 mm | ≤ 9.8 mm, **under the daughterboard** |
| U11 (DIP-8) | On Shore SA083000 (ED3038-ND) | 4.6 mm | ≤ 9.8 mm, outside |
| U1 Pico | Adafruit 5585 short sockets (1528-5585-ND) + 5584 short plug headers (1528-5584-ND) | 5.0 mm | Pico board at ~7.5 mm |

* All are machined (round-pin) sockets with 0.5 mm tails that fit the 0.8 mm DIP holes. LCSC equivalents
  (CONNFLY DS1001-01) are in the CSV.
* **Daughterboard clearance**: a Waveblaster daughterboard sits ~11 mm above the card. U2, U5, U6, U7 and U10 are
  under it, and a socketed DIP reaches ~9.8 mm (about 1.2 mm worst-case margin, 2 mm typical). That is fine for a
  daughterboard with a flat underside; if yours has parts underneath, solder those ICs directly, or use the
  low-profile Mill-Max 115-43-3xx-41-003000 sockets (2.41 mm; they need 1.0 mm holes, so the DIP footprints would
  need a change).
* **A socketed Pico has no USB host port** (J11) unless three short wires connect its TP1–TP3 to the holes under
  it. The Adafruit short sockets keep the Pico at ~7.5 mm; the standard 8.5 mm Sullins sockets at ~11–12 mm. The
  Pico's far end (x 167.38) is 2.9 mm under a full-size daughterboard's outline (x 170.32), so with a daughterboard
  fitted use the short sockets.

## Kept from v1.3.1

* **RV1** stays in the middle of the bracket end (at the top, its M7 bushing would be 0.4 mm above the PC's slot
  opening); v1.3.2 puts J5 (MIDI out) above it and J8 (line out) below it. **J11 at x 208.64** (at x 210 its flange
  stood 1.26 mm into the bracket plate). **C32/C33** (47 µF, 11 mm tall) stay out from under the daughterboard, now at
  x 184.62, and so do C22/C23 (10 µF, 11 mm) at the top next to J9 (C22's can 0.48 mm outside its outline). C1's can
  is about 0.4 mm from a full-size daughterboard's maximum outline at nominal size, 0.16 mm at maximum can size
  (v1.3.1: 0.68 / 0.43 mm; C1 moved 0.27 mm with the Pico row).
* No copper inside the gold-finger area: a no-fill rule area covers the strip above the fingers, and **J3's mask
  opening between the fingers starts 0.63 mm lower (y 129.6) than the finger tops**. Each finger also has its own
  mask opening, the size of the finger (from y 128.97, no mask expansion), so a track beside a finger top is
  covered only by the mask between them. Keep power copper at least 0.30 mm from the finger copper (this layout:
  0.42 mm or more, −12V next to B6 (DRQ2); signal tracks pass the finger tops at 0.24 mm). The ISA GND fingers B1,
  B10 and B31 each have a back-side track into the pour: B1's and B31's are 1.0 mm straight into it, B10's is 1.0 mm
  for 4.0 mm and then 0.5 mm for 2.6 mm (see [Known weaker points](#known-weaker-points-accepted)).
* **Don't run "Update footprint from library"** on J3 (the mask edit), J11 (the shield padstack below) or RV1 (the
  library footprint has a stray Edge.Cuts line that breaks the outline). DRC lists these three as
  `lib_footprint_mismatch` warnings; that is expected. J5, J8, RV1 and F1 also carry 3D models from `hw-common/parts`
  in place of stock model paths that KiCad 10's library does not have: updating them from the library puts the
  missing paths back. The two Pico micro-USB shell relief slots (1.3 × 2.0 mm) are
  drawn on Edge.Cuts as locked board items (JLCPCB wants non-plated slots on the outline layer), and five rule
  areas keep vias and the front pour away from the Pico's test pads. On v1.3.2 they moved with U1 (1.62 mm left in
  all: 0.27 mm, then 1.35 mm for the 102 mm trim); **move them with U1 again if U1 ever moves**.
* J11's shield pad next to the Pico's top pin row has a 2.6 mm pad on the front (3.0 mm on the back). With the Pico
  1.35 mm further in, it faces Pico pin 3 (GND): 0.48 mm on the front (2.08 mm to the pin's THT pad on the back), so
  a bridge there is harmless. Pin 4 (SPI_SCK), which faced it at 0.48 mm on v1.3.1 and the routed layout, is now
  0.80 mm away. **Solder J11 before the Pico and check the gap to pin 4 for a bridge.** H2's mask opening is 0.3 mm
  smaller (it sits 0.38 mm from Pico pin 39).
* Rule areas keep copper tracks out of the front exposed-copper logo, and vias and the front GND pour out from under
  the flat Pico's test pads (TP4–TP6, Pico 2 TP7) and its TP1–TP3 USB area.
* U12's GND (pin 2) has a GND via 1.30 mm from the pin (the DIP-adapter layout: 1.26 mm); keep one there.
* A `JLCJLCJLCJLC` order-number placeholder sits on B.Fab next to the Pico (not plotted). No via hole touches its
  box (the nearest, a GND via, is 0.45 mm below it). If an order ever uses "Specify a location", check the box for
  via holes again after any routing change.

## Unchanged from v1.3.1

### USB host port (J11, sheet 4 "USB host port")

A USB-A host port at the bracket for a mouse, joystick, keyboard, flash drive (CD-ROM images) or a hub, as on the
PicoGUS NE2000 card and the PicoMEM 2.

* **Data**: straight from the Pico's own USB D+/D− test points **TP3 / TP2** (behind the Pico's 27 Ω series
  resistors). U1 uses `RPi_Pico_SMD_TH_USB_NoSWD`: the v1.3.0 Pico footprint plus three plated holes under TP1
  (GND), TP2 (D−) and TP3 (D+), without the SMD pads at the SWD end (v1.3.1: `RPi_Pico_SMD_TH_USB`, with them). The
  Pico must be **soldered flat** (castellated edge or through-hole pins, no header) so
  the three pads can be soldered from the back of the card. The positions are the same on Pico, Pico 2, Pico W and
  Pico 2 W. On headers or in a socket, solder three short wires (26–30 AWG, under 3 cm) from TP1–TP3 into the holes,
  or use the micro-USB OTG route of v1.3.0. The Pico's micro-USB stays in parallel with J11: **use one or the other.**
  TP2 = D− and TP3 = D+ were checked against Raspberry Pi's Pico R3 schematic and KiCad's own Pico footprint.
* **J11**: Molex 67643 (0676430910, DigiKey WM4993-ND / LCSC C2798029), stock footprint
  `Connector_USB:USB_A_Molex_67643_Horizontal`. Its front lip (14.4 × 7.16 mm, the frontmost part, 12.99 mm in
  front of the pin row) sits 0.1 mm behind the inside of the bracket plate. It is larger than the 13.6 × 6.2 mm
  cut-out, so it is the panel stop: nothing of J11 enters the cut-out, only the USB plug comes in through it. The
  receptacle face is 0.9 mm behind the outside of the bracket (PicoGUS 2.0: 1.3 mm), see [Bracket](#bracket).
* **VBUS**: ISA +5 V through **F1** (Bourns MF-R050, 0.5 A hold) with C34 (220 µF low-impedance; USB 2.0 asks for
  ≥ 120 µF) and C35 (0.1 µF), always on, like the PicoMEM 2's USB-A port. The Pico's VBUS pin (J7) is not involved.
* **U12** (USBLC6-2SC6, SOT-23-6): optional ESD protection on D+/D−, routed flow-through as on v1.3.1: D+ J11 →
  pin 6 → under the body → pin 1, D− pin 4 → pin 3, on to the Pico, so there are no stubs and the port works without
  U12. On v1.3.2 it sits next to U8, about 10 mm west of J11's pins (F1 between), with C35 (0.1 µF) just below it.
  Pin 1 is marked by the footprint's silk triangle just above it (v1.3.1's hand-placed dot is removed). **If you fit
  U12, solder it before C35**, 0.36 mm below it.
* USB-C was considered and left out: the PicoMEM 2 also uses USB-A for its host port and USB-C only for
  programming (5.1k Rd, never sourcing VBUS). A dual USB-A/USB-C footprint is in the shared library, unused.

### Waveblaster header without standoff holes

J9 uses `PiGUS library:Wavetable_NoMountingHoles`: the v1.3.0 `Wavetable` footprint without the two 3.2 mm
daughterboard standoff holes (the far one landed in U4 in the rev B placement). The daughterboard is held by the
2x13 header only, so there is no M3 standoff and no screws in the BOM. A full-size daughterboard overhangs the
card's far end; support it by hand when plugging/unplugging cables.

### Bracket

The bracket parts are where v1.3.1 had them, not where v1.3.0 (and v1.2) had them. **The tab holes H1/H2 are
1.70 mm further from the plate than on a Keystone 9202**: their centres are 7.03 mm behind the plate's inner face
instead of 5.33 mm (measured on the board's bracket drawing on User.Drawings), because the card is 1.84 mm shorter
at the bracket end (see [102 mm board](#102-mm-board)). A stock Keystone 9202, a PicoGUS 2.0 bracket and the brackets
for v1.2, v1.3.0, v1.3.1 and the routed v1.3.2 layout therefore do not fit: the card needs a bracket with tabs
1.70 mm longer, e.g. a 3D-printed one (the bracket drawing on User.Drawings has them). The plate itself sits where
it always does in the case, so the openings do not change. Hole positions (distances measured down from the
bracket's top surface, height = centre above the card's component side):

| Part | Hole | Down from the bracket top | Height |
|---|---|---|---|
| J5 MIDI out | Ø6.3–6.5 mm | 14.9 mm | 7.0 mm |
| RV1 WT volume (M7 bushing) | Ø7.2–7.5 mm | 23.9 mm | 6.5 mm |
| J8 line out | Ø6.3–6.5 mm | 41.4 mm | 7.0 mm |
| J11 USB-A | 13.6 × 6.2 mm rectangle, corners R ≤ 0.5 | 54.0 mm (centre; the cut-out runs from 47.2 to 60.8 mm) | 1.0–7.2 mm (centre 4.1) |

* All four are inside the PC/AT slot opening (it starts 10.95 mm below the bracket top). A jack is on top because its
  Ø6 nose fits there; RV1's M7 nut needs the room further down. MIDI OUT (J5) is on top and LINE OUT (J8) below
  RV1 (the DIP-adapter layout had them the other way round).
* No hole for the Pico's micro-USB: its plug can't enter the slot opening. Flash the Pico before soldering it,
  or with `pgusinit`.
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
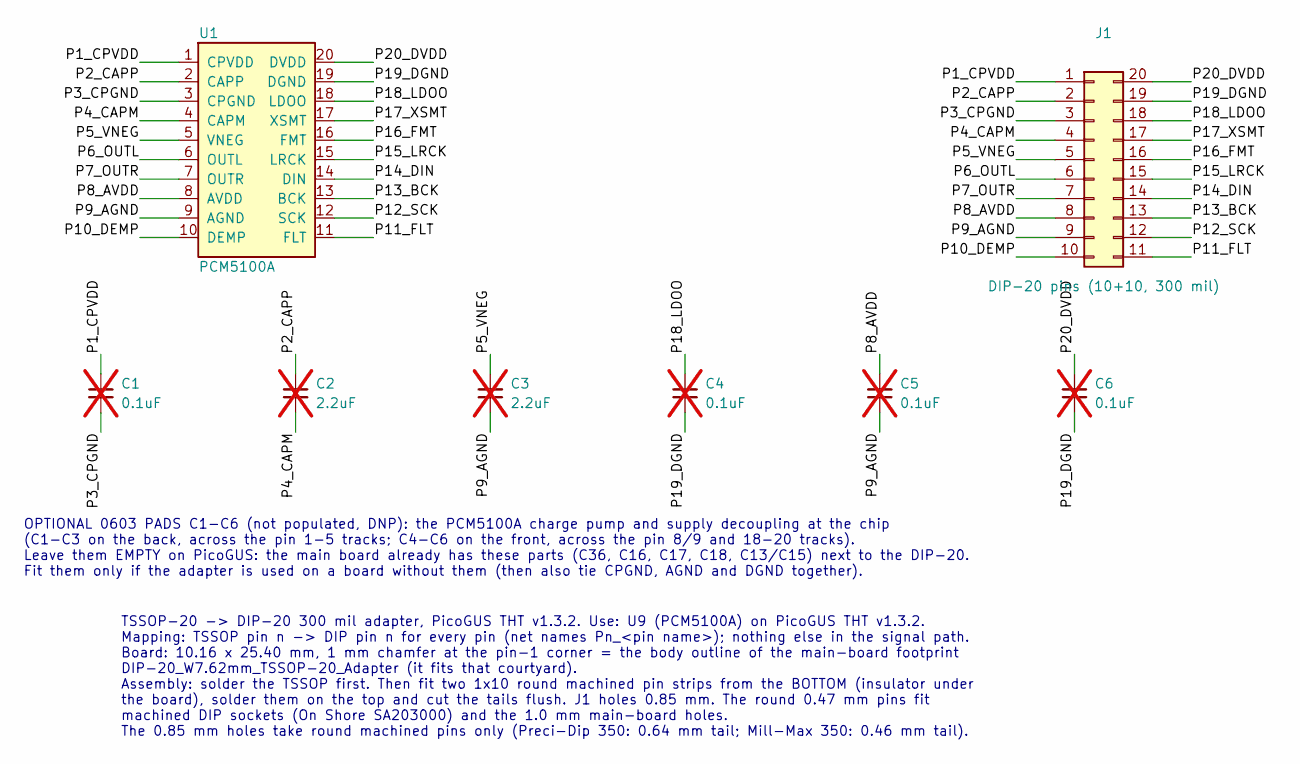
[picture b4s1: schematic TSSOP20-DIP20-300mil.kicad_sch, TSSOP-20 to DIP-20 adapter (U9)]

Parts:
C1, C4, C5, C6: 0.1uF; C_0603_1608Metric; MPN CL10B104KB8NNNC; LCSC C1591; not fitted
C2, C3: 2.2uF; C_0603_1608Metric; MPN CL10A225KO8NNNC; LCSC C23630; not fitted
J1: DIP-20 pins (10+10, 300 mil); DIP-20_W7.62mm_AdapterPins_Drill0.85; MPN 350-10-110-00-001101 (x2); DigiKey 350-10-110-00-001101-ND (x2)
U1: PCM5100A; TSSOP-20_4.4x6.5mm_P0.65mm_HandSolder_DIP300; MPN PCM5100APWR; LCSC C131154

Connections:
/P1_CPVDD: C1.1, J1.1, U1.1 (CPVDD)
/P2_CAPP: C2.1, J1.2, U1.2 (CAPP)
/P3_CPGND: C1.2, J1.3, U1.3 (CPGND)
/P4_CAPM: C2.2, J1.4, U1.4 (CAPM)
/P5_VNEG: C3.1, J1.5, U1.5 (VNEG)
/P6_OUTL: J1.6, U1.6 (OUTL)
/P7_OUTR: J1.7, U1.7 (OUTR)
/P8_AVDD: C5.1, J1.8, U1.8 (AVDD)
/P9_AGND: C3.2, C5.2, J1.9, U1.9 (AGND)
/P10_DEMP: J1.10, U1.10 (DEMP)
/P11_FLT: J1.11, U1.11 (FLT)
/P12_SCK: J1.12, U1.12 (SCK)
/P13_BCK: J1.13, U1.13 (BCK)
/P14_DIN: J1.14, U1.14 (DIN)
/P15_LRCK: J1.15, U1.15 (LRCK)
/P16_FMT: J1.16, U1.16 (FMT)
/P17_XSMT: J1.17, U1.17 (XSMT)
/P18_LDOO: C4.1, J1.18, U1.18 (LDOO)
/P19_DGND: C4.2, C6.2, J1.19, U1.19 (DGND)
/P20_DVDD: C6.1, J1.20, U1.20 (DVDD)

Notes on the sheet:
OPTIONAL 0603 PADS C1-C6 (not populated, DNP): the PCM5100A charge pump and supply decoupling at the chip (C1-C3 on the back, across the pin 1-5 tracks; C4-C6 on the front, across the pin 8/9 and 18-20 tracks). Leave them EMPTY on PicoGUS: the main board already has these parts (C36, C16, C17, C18,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
TSSOP-20 -> DIP-20 300 mil adapter, PicoGUS THT v1.3.2. Use: U9 (PCM5100A) on PicoGUS THT v1.3.2. Mapping: TSSOP pin n -> DIP pin n for every pin (net names Pn_<pin name>); nothing else in the signal path. Board: 10.16 x 25.40 mm, 1 mm chamfer at the pin-1 corner = the body outline of the main-boar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

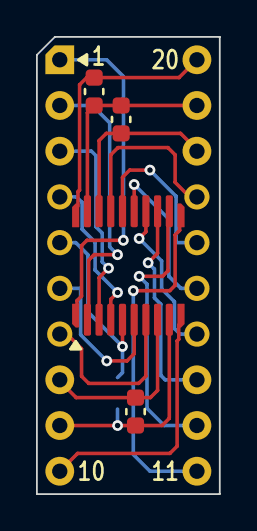
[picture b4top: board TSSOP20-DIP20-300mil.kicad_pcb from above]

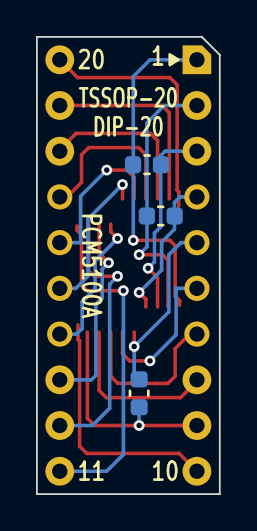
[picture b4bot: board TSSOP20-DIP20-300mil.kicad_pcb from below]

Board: 2 copper layers, 10.2 x 25.4 mm, 8 parts (3 on the bottom side), 20 nets.

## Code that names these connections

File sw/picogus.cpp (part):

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#ifdef ASYNC_UART
#include "stdio_async_uart.h"
#endif 
// UART_TX_PIN is defined in isa_io.pio.h
#define UART_RX_PIN (-1)
#define UART_ID     uart0
#define BAUD_RATE   230400
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    busy_wait_ms(250);
    overclock_370mhz();
#ifdef ASYNC_UART
    stdio_async_uart_init_full(UART_ID, BAUD_RATE, UART_TX_PIN, UART_RX_PIN);
#else
    stdio_init_all();
#endif
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    if (*reset_reason & VREG_AND_CHIP_RESET_CHIP_RESET_HAD_POR_BITS) {
        DBG_PUTS("I was reset due to power on reset or brownout detection.");
    } else if (*reset_reason & VREG_AND_CHIP_RESET_CHIP_RESET_HAD_RUN_BITS) {
        DBG_PUTS("I was reset due to the RUN pin (either manually or due to ISA RESET signal)");
    } else if(*reset_reason & VREG_AND_CHIP_RESET_CHIP_RESET_HAD_PSM_RESTART_BITS) {
        DBG_PUTS("I was reset due the debug port");
    }
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    web_init_core0();
#endif

    // Determine board type. GPIO 29 is grounded on PicoGUS v2.0, and on a Pico, it's VSYS/3 (~1.666V)
    // GPIO 25 must be high to read GPIO 29 on the Pico W
    gpio_init(25);
    gpio_set_dir(25, GPIO_OUT);
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    if (BOARD_TYPE == PICO_BASED) {
        // Original hardware drives MIDI directly from RP2040. Newer HW uses an open drain inverter
        // PicoGUS v1.2 also uses an open drain but we can't detect that particular board
        gpio_set_drive_strength(UART_TX_PIN, GPIO_DRIVE_STRENGTH_12MA);
    }
    gpio_set_function(UART_TX_PIN, GPIO_FUNC_UART);
#endif // SOUND_MPU

#ifdef PSRAM_CORE0
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    for(int i=AD0_PIN; i<(AD0_PIN + 10); ++i) {
        gpio_disable_pulls(i);
    }
    gpio_disable_pulls(IOW_PIN);
    gpio_disable_pulls(IOR_PIN);
    gpio_pull_down(IOCHRDY_PIN);
    gpio_set_dir(IOCHRDY_PIN, GPIO_OUT);

    DBG_PUTS("Enabling bus transceivers...");
    // waggle ADS to set BUSOE latch
    gpio_init(ADS_PIN);
    gpio_set_dir(ADS_PIN, GPIO_OUT);
    gpio_put(ADS_PIN, 1);
    busy_wait_ms(10);
    gpio_put(ADS_PIN, 0);

    DBG_PUTS("Starting ISA bus PIO...");
    // gpio_set_drive_strength(ADS_PIN, GPIO_DRIVE_STRENGTH_12MA);
    gpio_set_slew_rate(ADS_PIN, GPIO_SLEW_RATE_FAST);

    uint iow_offset = pio_add_program(pio0, &iow_program);
    pio_sm_claim(pio0, IOW_PIO_SM);
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
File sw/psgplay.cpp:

/*
 *  Copyright (C) 2022-2024  Ian Scott
 *
 *  This program is free software; you can redistribute it and/or modify
 *  it under the terms of the GNU General Public License as published by
 *  the Free Software Foundation; either version 2 of the License, or
 *  (at your option) any later version.
 *
 *  This program is distributed in the hope that it will be useful,
 *  but WITHOUT ANY WARRANTY; without even the implied warranty of
 *  MERCHANTABILITY or FITNESS FOR A PARTICULAR PURPOSE.  See the
 *  GNU General Public License for more details.
 *
 *  You should have received a copy of the GNU General Public License along
 *  with this program; if not, write to the Free Software Foundation, Inc.,
 *  51 Franklin Street, Fifth Floor, Boston, MA 02110-1301, USA.
 */

#include "include/pg_debug.h"

#if PICO_ON_DEVICE
#include "hardware/clocks.h"
#include "hardware/structs/clocks.h"
#include "hardware/pwm.h"
#include "hardware/pio.h"
#endif

#include "pico/stdlib.h"
#include "audio/audio_i2s_minimal.h"
#include "audio/volctrl.h"
#include "audio/clamp.h"

#include "square/square.h"

#include "include/cmd_buffers.h"

#if SOUND_TANDY
extern tandy_buffer_t tandy_buffer;
#endif
#if SOUND_CMS
extern cms_buffer_t cms_buffer;
#endif

extern uint LED_PIN;

#ifdef USB_STACK
#include "tusb.h"
#endif
#if defined(USB_MOUSE) || defined(SOUND_MPU)
#include "system/pico_pic.h"
#endif

#ifdef USB_MOUSE
#include "mouse/8250uart.h"
#include "mouse/sermouse.h"
#endif

#if PICO_ON_DEVICE
#include "pico/binary_info.h"
bi_decl(bi_3pins_with_names(PICO_AUDIO_I2S_DATA_PIN, "I2S DIN", PICO_AUDIO_I2S_CLOCK_PIN_BASE, "I2S BCK", PICO_AUDIO_I2S_CLOCK_PIN_BASE+1, "I2S LRCK"));
#endif

#ifdef SOUND_MPU
#include "system/flash_settings.h"
extern Settings settings;
#include "mpu401/export.h"
#endif

#ifdef WEBSERVER
#include "web/web.h"
#endif

#define audio_pio __CONCAT(pio, PICO_AUDIO_I2S_PIO)

static void init_audio(void) {
    const audio_i2s_config_t config = {
            .data_pin = PICO_AUDIO_I2S_DATA_PIN,
            .clock_pin_base = PICO_AUDIO_I2S_CLOCK_PIN_BASE,
            .dma_channel = 6,
            .pio_sm = PICO_AUDIO_I2S_SM,
    };
    audio_i2s_minimal_setup(&config, 44100);
}

#if SOUND_TANDY
static tandysound_t tandysound;
#endif
#if SOUND_CMS
static cms_t cms;
#endif

// Setup values for audio sample clock
static constexpr uint32_t clocks_per_sample_minus_one = (RP2_CLOCK_SPEED * 1000u / 44100) - 1;
static constexpr uint pwm_slice_num = 4; // slices 0-3 are taken by USB joystick support

// PSG generation is cheap (phase accumulators + volume lookups per voice), so
// synthesize directly in the ISR — no intermediate FIFO needed.
void audio_sample_handler(void) {
    pwm_clear_irq(pwm_slice_num);

    int32_t buf[2] = {0, 0};
#if SOUND_TANDY
    tandysound.generator().generate_frames(buf, 1);
#endif
#if SOUND_CMS
    cms.generator(0).generate_frames(buf, 1);
    cms.generator(1).generate_frames(buf, 1);
#endif
    int32_t sample_l = scale_sample(clamp16(buf[0]), volume.psg, 0);
    int32_t sample_r = scale_sample(clamp16(buf[1]), volume.psg, 0);
    sample_l = clamp16(sample_l);
    sample_r = clamp16(sample_r);

    audio_pio->txf[PICO_AUDIO_I2S_SM] = ((sample_l & 0xFFFF) | (sample_r << 16));
}

void play_psg() {
    DBG_PUTS("starting core 1 psg");
    // flash_safe_execute_core_init();

#if defined(USB_MOUSE) || defined(SOUND_MPU)
    // Init PIC on this core so it handles timers
    PIC_Init();
    DBG_PUTS("pic inited on core 1");
#endif
#ifdef USB_STACK
    // Init TinyUSB for joystick support
    tuh_init(BOARD_TUH_RHPORT);
    // Pump USB events for ~500 ms so any device already connected at boot
    // is fully enumerated before the audio loop starts.
    {
        uint32_t deadline = time_us_32() + 500000u;
        while (time_us_32() < deadline) tuh_task();
    }
#endif

#ifdef SOUND_MPU
    MPU401_Init(settings.MPU.delaySysex, settings.MPU.fakeAllNotesOff);
#endif

    init_audio();
    set_volume(CMD_PSGVOL);

    // Use the PWM peripheral to trigger an IRQ at 44100Hz
    pwm_config pwm_c = pwm_get_default_config();
    pwm_config_set_wrap(&pwm_c, clocks_per_sample_minus_one);
    pwm_init(pwm_slice_num, &pwm_c, false);
    pwm_set_irq_enabled(pwm_slice_num, true);
    irq_set_exclusive_handler(PWM_IRQ_WRAP, audio_sample_handler);
    irq_set_priority(PWM_IRQ_WRAP, PICO_LOWEST_IRQ_PRIORITY);
    irq_set_enabled(PWM_IRQ_WRAP, true);
    pwm_set_enabled(pwm_slice_num, true);

    for (;;) {
        bool notfirst = false;
#if SOUND_TANDY
        while (tandy_buffer.tail != tandy_buffer.head) {
            if (!notfirst) {
                gpio_xor_mask(LED_PIN);
                notfirst = true;
            }
            tandysound.write_register(0, tandy_buffer.cmds[tandy_buffer.tail]);
            ++tandy_buffer.tail;
        }
#endif // SOUND_TANDY
#if SOUND_CMS
        while (cms_buffer.tail != cms_buffer.head) {
            if (!notfirst) {
                gpio_xor_mask(LED_PIN);
                notfirst = true;
            }
            auto cmd = cms_buffer.cmds[cms_buffer.tail];
            if (cmd.addr & 1) {
                cms.write_addr(cmd.addr, cmd.data);
            } else {
                cms.write_data(cmd.addr, cmd.data);
            }
            ++cms_buffer.tail;
        }
#endif

#ifdef USB_STACK
        // Service TinyUSB events
        tuh_task();
#endif
#ifdef USB_MOUSE
        // mouse task
        sermouse_core1_task();

        // uart emulation task
        uartemu_core1_task();
#endif
#ifdef SOUND_MPU
        send_midi_bytes(8);
#endif
#ifdef WEBSERVER
        // Lowest priority work: PSG audio is synthesized in an interrupt
        web_task();
#endif
    }
}
